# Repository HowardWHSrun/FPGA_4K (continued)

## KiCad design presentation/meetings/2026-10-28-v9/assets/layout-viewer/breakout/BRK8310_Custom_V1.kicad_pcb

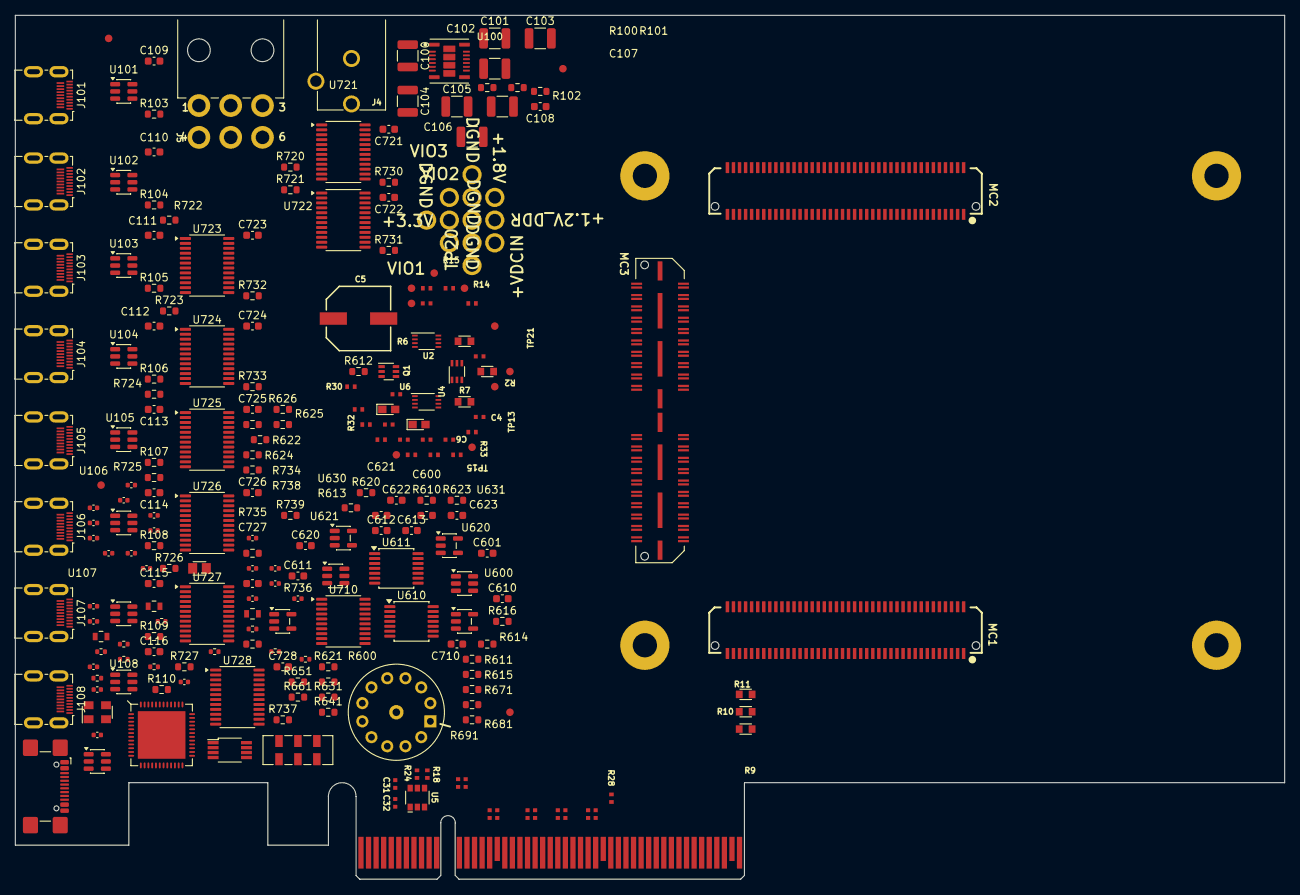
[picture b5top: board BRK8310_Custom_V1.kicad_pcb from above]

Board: 4 copper layers, 167.6 x 114.1 mm, 247 parts (0 on the bottom side), 224 nets, no tracks yet.

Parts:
C4: C0402C104K8PACTU; BRK8310_C4
C5: EEE-FK1E221P; BRK8310_C5
C6: TMK105BJ104KV-F; BRK8310_C6
C7: C0402C104K8PACTU; BRK8310_C7
C8: C0402C104K8PACTU; BRK8310_C8
C9: C0402C104K8PACTU; BRK8310_C9
C10: C0402C104K8PACTU; BRK8310_C10
C11: C0402C104K8PACTU; BRK8310_C11
C12: C0402C104K8PACTU; BRK8310_C12
C13: C0402C104K8PACTU; BRK8310_C13
C14: C0402C104K8PACTU; BRK8310_C14
C15: C0402C104K8PACTU; BRK8310_C15
C16: C0402C104K8PACTU; BRK8310_C16
C17: C0402C104K8PACTU; BRK8310_C17
C18: C0402C104K8PACTU; BRK8310_C18
C19: C0402C104K8PACTU; BRK8310_C19
C20: C0402C104K8PACTU; BRK8310_C20
C27: C0402C104K8PACTU; BRK8310_C27
C28: C0402C104K8PACTU; BRK8310_C28
C31: C0402C104K8PACTU; BRK8310_C31
C32: C0402C104K8PACTU; BRK8310_C32
C100, C101, C102, C103: 10uF 50V X7R; C_1210_3225Metric
C104, C105, C106, C107: 47uF 16V X6S; C_1210_3225Metric
C108: 47pF C0G; C_0603_1608Metric
C109, C110, C111, C112, C113, C114, C115, C116: 0.1uF 16V; C_0603_1608Metric
C500: 4.7u; C500
C501: 100n; C501
C502: 100n; C502
C503: 18p; C503
C504: 18p; C504
C505: 100n; C505
C506: 10n; C506
C507: 4.7u; C507
C508: 100n; C508
C509: 100n; C509
C510: 100n; C510
C511: 100n; C511
C512: 4.7u; C512
C513: 4.7u; C513
C514: 100n; C514
C515: 4.7u; C515
C516: 100n; C516
C517: 100n; C517
C518: 100n; C518
C519: 10n; C519
C520: 2.2uF 10V X7R; C520
C521: 2.2uF 10V X7R; C521
C600, C601: 2.2uF / 10V; C_0603_1608Metric
C610, C611, C612, C613, C620, C621, C622, C623, C710, C721, C722, C723, C724, C725, C726, C727, C728: 100nF / 16V; C_0603_1608Metric
D1: +3.3VDD; BRK8310_D1
D2: +VDC; BRK8310_D2
D500: USBLC6-2SC6; D500
FB500: 600R; FB500
FB501: 600R; FB501
FB502: 600R; FB502
FB503: 220R @100MHz; FB503
FID1: FIDUCIAL; BRK8310_FID1
FID2: FIDUCIAL; BRK8310_FID2
FID3: FIDUCIAL; BRK8310_FID3
FID4: FIDUCIAL; BRK8310_FID4
J4: PJ-102AH; BRK8310_J4
J5: 0455580003; BRK8310_J5
J6: PCIe x8 Card-Edge Connector; BRK8310_J6
J101, J102, J103, J104, J105, J106, J107, J108: Molex 467651001; HDMI_Micro-D_Molex_46765-1xxx
J500: USB4110-GF-A; J500
MC1: BTE-040-01-F-D-A; BRK8310_MC1
MC2: BTE-040-01-F-D-A; BRK8310_MC2
MC3: QTH-040-01-F-D-DP-A; BRK8310_MC3
MH1: MTG; BRK8310_MH1
MH2: MTG; BRK8310_MH2
MH3: MTG; BRK8310_MH3
MH4: MTG; BRK8310_MH4
Q1: SI1922EDH-T1-GE3; BRK8310_Q1
R2: CRCW06030000Z0EA; BRK8310_R2
R3: CRCW0402549RFKED; BRK8310_R3
R4: CRCW04022K00FKED; BRK8310_R4
R6: CRCW06030000Z0EA; BRK8310_R6
R7: CRCW06030000Z0EA; BRK8310_R7
R9: CRCW06030000Z0EA; BRK8310_R9
R10: CRCW06030000Z0EA; BRK8310_R10
R11: CRCW06030000Z0EA; BRK8310_R11
R13: CRCW0402200KFKED; BRK8310_R13
R14: CRCW04024K75FKED; BRK8310_R14
R15: CRCW04024K75FKED; BRK8310_R15
R18: CRCW0402100KFKED; BRK8310_R18
R23: CRCW0402200KFKED; BRK8310_R23
R24: CRCW0402100KFKED; BRK8310_R24
R25: CRCW0402100KFKED; BRK8310_R25
R28: CRCW04020000Z0ED; BRK8310_R28
R30: CRCW04024K75FKED; BRK8310_R30
R31: CRCW04024K75FKED; BRK8310_R31
R32: CRCW0402100KFKED; BRK8310_R32
R33: CRCW0402100KFKED; BRK8310_R33
R100: 23.2k 1%; R_0603_1608Metric
R101: 10k 1%; R_0603_1608Metric
R102: 17.4k 1%; R_0603_1608Metric
R103, R104, R105, R106, R107, R108, R109, R110: 37.4k 1%; R_0603_1608Metric
R500: 5.1k 1%; R500
R501: 5.1k 1%; R501
R502: 100k; R502
R503: 100k; R503
R504: 2k; R504
R505: 10k; R505
R506: 10k; R506
R507: 12k 1%; R507
R508: 10k; R508
R509: 10k; R509
R600, R610, R611, R620, R621, R631, R641, R651, R661, R671, R681, R691, R720, R721, R722, R723, R724, R725, R726, R727: 10k / 1%; R_0603_1608Metric
R612: 1M / 1%; R_0603_1608Metric
R613, R623: 100k / 1%; R_0603_1608Metric
R614, R615, R616, R624, R625, R626: 33R / 1%; R_0603_1608Metric
R622: 68k / 1%; R_0603_1608Metric
R730, R731, R732, R733, R734, R735, R736, R737: 1k / 1%; R_0603_1608Metric
R738: 140k / 0.1%; R_0603_1608Metric
R739: 49.9k / 0.1%; R_0603_1608Metric
SW600: Grayhill56P30_1P12T_N; Grayhill_56P30_1P12T_N
SW700: JS202011JCQN; SW700
TP1: +VDCIN; BRK8310_TP1
TP2: +3.3V; BRK8310_TP2
TP3: +1.8V; BRK8310_TP3
TP4: +1.2V_DDR; BRK8310_TP4
TP5: DGND; BRK8310_TP5
TP6: DGND; BRK8310_TP6
TP7: DGND; BRK8310_TP7
TP8: DGND; BRK8310_TP8
TP9: SMDAT_VIO; BRK8310_TP9
TP10: SMDAT_PCIE; BRK8310_TP10
TP11: SMCLK_PCIE; BRK8310_TP11
TP12: SMCLK_VIO; BRK8310_TP12
TP13: PERST_VIO; BRK8310_TP13
TP14: PERST_PCIE; BRK8310_TP14
TP15: WAKE_VIO; BRK8310_TP15
TP16: WAKE_PCIE; BRK8310_TP16
TP17: VIO1; BRK8310_TP17
TP18: VIO2; BRK8310_TP18
TP19: VIO3; BRK8310_TP19
TP20: +12V_PCIE_C; BRK8310_TP20
TP21: FAULT; BRK8310_TP21
U2: PCA9306DCUR; BRK8310_U2
U4: SN74AXC1T45DCK; BRK8310_U4
U5: AP22653AW6-7; BRK8310_U5
U6: PCA9306DCUR; BRK8310_U6
U100: TPSM63606RDLR; TI_TPSM63606_RDL0020A_EVM
U101, U102, U103, U104, U105, U106, U107, U108: TPS2553DBVR; SOT-23-6
U501: FT232HQ; U501
U505: 93LC56B-E/MS; U505
U506: TLV75533PDBVR; U506
U600: TLV75518PDBVR; SOT-23-5
U610, U611: TXU0304PWR; TSSOP-14_4.4x5mm_P0.65mm
U620: TPS3808G18DBVR; SOT-23-6
U621: TPS3808G01DBVR; SOT-23-6
U630, U631: SN74LVC1G17DBVR; SOT-23-5
U710: SN74LVC540APWR; TSSOP-20_4.4x6.5mm_P0.65mm
U721, U722, U723, U724, U725, U726, U727, U728: TS3A27518EPWR; TSSOP-24_4.4x7.8mm_P0.65mm
Y500: 12MHz; Y500

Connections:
+1.2V_DDR: MC3.80, R2.2, TP4.1
+1.8V: C4.1, MC1.2, R612.1, TP3.1, U620.5
+3.3V: MC2.70, R3.2, R30.2, R31.2, TP2.1
+3.3VAUX_PCIE: C31.2, R13.2, R23.2, U5.6
+3.3VAUX_PCIE_C: C32.2, J6.B10, R18.2, U5.1
+3.3V_PCIE_C: C12.2, J6.A9, J6.A10, J6.B8, U4.6
+VDCIN: C5.1, C6.2, C100.1, C101.1, C102.1, C103.1, J4.1, J5.1, J5.2, J5.3, MC2.1, MC2.2, MC2.3, MC2.4, R4.2, TP1.1, U100.1, U100.14, U100.16
/B64_L17N: MC1.44, R11.2
/B64_L17P: MC1.42, R10.2
/B64_L20N: MC1.40, R9.2
/B67_T3U_N12: MC3.78, R7.2
/Frontend ports and power/FRONTEND_3V3: C104.1, C105.1, C106.1, C107.1, C108.2, C109.1, C110.1, C111.1, C112.1, C113.1, C114.1, C115.1, C116.1, R100.2, U100.5, U100.8, U100.9, U101.1, U101.3, U102.1, U102.3, U103.1, U103.3, U104.1, U104.3, U105.1, U105.3, U106.1, U106.3, U107.1, U107.3, U108.1, U108.3
/Frontend ports and power/P1_TCK: J101.17, R730.1, U721.11
/Frontend ports and power/P1_TDI: J101.15, U721.13
/Frontend ports and power/P1_TDO: J101.18, U721.17
/Frontend ports and power/P1_TMS: J101.2, U721.15
/Frontend ports and power/P1_VREF: J101.1, U721.18
/Frontend ports and power/P2_TCK: J102.17, R731.1, U722.11
/Frontend ports and power/P2_TDI: J102.15, U722.13
/Frontend ports and power/P2_TDO: J102.18, U722.17
/Frontend ports and power/P2_TMS: J102.2, U722.15
/Frontend ports and power/P2_VREF: J102.1, U722.18
/Frontend ports and power/P3_TCK: J103.17, R732.1, U723.11
/Frontend ports and power/P3_TDI: J103.15, U723.13
/Frontend ports and power/P3_TDO: J103.18, U723.17
/Frontend ports and power/P3_TMS: J103.2, U723.15
/Frontend ports and power/P3_VREF: J103.1, U723.18
/Frontend ports and power/P4_TCK: J104.17, R733.1, U724.11
/Frontend ports and power/P4_TDI: J104.15, U724.13
/Frontend ports and power/P4_TDO: J104.18, U724.17
/Frontend ports and power/P4_TMS: J104.2, U724.15
/Frontend ports and power/P4_VREF: J104.1, U724.18
/Frontend ports and power/P5_TCK: J105.17, R734.1, U725.11
/Frontend ports and power/P5_TDI: J105.15, U725.13
/Frontend ports and power/P5_TDO: J105.18, U725.17
/Frontend ports and power/P5_TMS: J105.2, U725.15
/Frontend ports and power/P5_VREF: J105.1, U725.18
/Frontend ports and power/P6_TCK: J106.17, R735.1, U726.11
/Frontend ports and power/P6_TDI: J106.15, U726.13
/Frontend ports and power/P6_TDO: J106.18, U726.17
/Frontend ports and power/P6_TMS: J106.2, U726.15
/Frontend ports and power/P6_VREF: J106.1, U726.18
/Frontend ports and power/P7_TCK: J107.17, R736.1, U727.11
/Frontend ports and power/P7_TDI: J107.15, U727.13
/Frontend ports and power/P7_TDO: J107.18, U727.17
/Frontend ports and power/P7_TMS: J107.2, U727.15
/Frontend ports and power/P7_VREF: J107.1, U727.18
/Frontend ports and power/P8_TCK: J108.17, R737.1, U728.11
/Frontend ports and power/P8_TDI: J108.15, U728.13
/Frontend ports and power/P8_TDO: J108.18, U728.17
/Frontend ports and power/P8_TMS: J108.2, U728.15
/Frontend ports and power/P8_VREF: J108.1, U728.18
/PCIE X4/+12V_PCIE_C: J6.A2, J6.A3, J6.B1, J6.B2, J6.B3, TP20.1
/PCIE X4/PCIE_PERST_B_3V3: J6.A11, TP14.1, U4.4
/PCIE X4/PCIE_PERST_VIO: C11.2, R2.1, U4.1
/PCIE X4/PCIE_PRSNT1_B: J6.A1, R28.2
/PCIE X4/PCIE_REFCLKN_C: C8.1, J6.A14
/PCIE X4/PCIE_REFCLKP_C: C7.1, J6.A13
/PCIE X4/PCIE_RX0N_C: C14.1, J6.A17
/PCIE X4/PCIE_RX0P_C: C13.1, J6.A16
/PCIE X4/PCIE_RX1N_C: C16.1, J6.A22
/PCIE X4/PCIE_RX1P_C: C15.1, J6.A21
/PCIE X4/PCIE_RX2N_C: C18.1, J6.A26
/PCIE X4/PCIE_RX2P_C: C17.1, J6.A25
/PCIE X4/PCIE_RX3N_C: C20.1, J6.A30
/PCIE X4/PCIE_RX3P_C: C19.1, J6.A29
/PCIE X4/PCIE_SMCLK_3V3: J6.B5, TP11.1, U2.5
/PCIE X4/PCIE_SMDAT_3V3: J6.B6, TP10.1, U2.6
/PCIE X4/PCIE_WAKE_B_3V3: J6.B11, TP16.1, U6.6
/PCIE X4/VIO_PG: Q1.3, R31.1, R32.2, U5.3
/PCIE_PERST_B_VIO: R7.1, TP13.1, U4.3
/PCIE_SMCLK_VIO: R11.1, R14.1, TP12.1, U2.4
/PCIE_SMDAT_VIO: R10.1, R15.1, TP9.1, U2.3
/PCIE_WAKE_B_VIO: R9.1, R25.1, TP15.1, U6.3
/USB JTAG and selection/FTDI3V3_PHY: C515.1, C516.1, FB501.2, U501.3
/USB JTAG and selection/FTDI3V3_PLL: C513.1, C514.1, FB500.2, U501.8
/USB JTAG and selection/FTDI5V_FILTERED: C500.1, C501.1, FB502.2, U501.40
/USB JTAG and selection/FTDI_EECLK: R503.2, U501.44, U505.2
/USB JTAG and selection/FTDI_EECS: R502.1, U501.45, U505.1
/USB JTAG and selection/FTDI_EEDATA: R504.1, U501.43, U505.3
/USB JTAG and selection/HS_SENSE_DIV: R738.2, R739.2, U621.5
/VREFP: MC2.79, R6.2
B64_L1N: J101.14, MC1.12
B64_L1P: J101.12, MC1.10
B64_L2N: J102.14, MC1.16
B64_L2P: J102.12, MC1.14
B64_L3N: J103.14, MC1.15
B64_L3P: J103.12, MC1.13
B64_L4N: J104.14, MC1.8
B64_L4P: J104.12, MC1.6
B64_L5N: J105.14, MC1.7
B64_L5P: J105.12, MC1.5
B64_L6N: J106.14, MC1.11
B64_L6P: J106.12, MC1.9
B64_L7N: J107.14, MC1.23
B64_L7P: J107.12, MC1.21
B64_L8N: J108.14, MC1.20
B64_L8P: J108.12, MC1.18
DGND: C4.2, C5.2, C6.1, C9.1, C10.1, C11.1, C12.1, C27.1, C28.1, C31.1, C32.1, C100.2, C101.2, C102.2, C103.2, C104.2, C105.2, C106.2, C107.2, C109.2, C110.2, C111.2, C112.2, C113.2, C114.2, C115.2, C116.2, C500.2, C501.2, C502.2, C503.2, C504.2, C505.2, C506.1, C507.2, C508.2, C509.2, C510.2, C511.2, C512.2, C513.2, C514.2, C515.2, C516.2, C517.1, C518.1, C519.2, C520.2, C521.2, C600.2, C601.2, C610.2, C611.2, C612.2, C613.2, C620.2, C621.2, C622.2, C623.2, C710.2, C721.2, C722.2, C723.2, C724.2, C725.2, C726.2, C727.2, C728.2, D1.1, D2.1, D500.2, FB503.1, J4.2, J5.4, J5.5, J5.6, J6.A4, J6.A12, J6.A15, J6.A18, J6.A20, J6.A23, J6.A24, J6.A27, J6.A28, J6.A31, J6.A34, J6.A37, J6.A38, J6.A41, J6.A42, J6.A45, J6.A46, J6.A49, J6.B4, J6.B7, J6.B13, J6.B16, J6.B18, J6.B21, J6.B22, J6.B25, J6.B26, J6.B29, J6.B32, J6.B35, J6.B36, J6.B39, J6.B40, J6.B43, J6.B44, J6.B47, J6.B49, J101.4, J101.7, J101.10, J101.13, J101.16, J102.4, J102.7, J102.10, J102.13, J102.16, J103.4, J103.7, J103.10, J103.13, J103.16, J104.4, J104.7, J104.10, J104.13, J104.16, J105.4, J105.7, J105.10, J105.13, J105.16, J106.4, J106.7, J106.10, J106.13, J106.16, J107.4, J107.7, J107.10, J107.13, J107.16, J108.4, J108.7, J108.10, J108.13, J108.16, J500.A1, J500.A12, J500.B1, J500.B12, MC1.3, MC1.29, MC1.30, MC1.59, MC1.60, MC1.77, MC1.78, MC2.5, MC2.6, MC2.7, MC2.8, MC2.33, MC2.34, MC2.67, MC2.68, MC2.73, MC3.0, Q1.1, Q1.4, R24.1, R32.1, R33.1, R101.2, R102.2, R103.2, R104.2, R105.2, R106.2, R107.2, R108.2, R109.2, R110.2, R500.1, R501.2, R502.2, R507.2, R600.2, R611.2, R612.2, R613.2, R621.1, R622.2, R623.2, R631.1, R641.1, R651.1, R661.1, R671.1, R681.1, R691.1, R730.2, R731.2, R732.2, R733.2, R734.2, R735.2, R736.2, R737.2, R739.1, SW700.3, TP5.1, TP6.1, TP7.1, TP8.1, U2.1, U4.2, U4.5, U5.2, U6.1, U100.6, U100.11, U100.17, U100.18, U100.19, U100.20, U101.2, U102.2, U103.2, U104.2, U105.2, U106.2, U107.2, U108.2, U501.4, U501.9, U501.10, U501.11, U501.22, U501.23, U501.35, U501.36, U501.41, U501.42, U501.47, U501.48, U501.PAD, U505.5, U506.2, U600.2, U610.7, U611.7, U620.2, U621.2, U630.3, U631.3, U710.1, U710.10, U710.19, U721.5, U722.5, U723.5, U724.5, U725.5, U726.5, U727.5, U728.5, Y500.2, Y500.4
FTDI3V3: C505.1, C507.1, C508.1, C509.1, C510.1, C511.1, C512.1, FB500.1, FB501.1, R503.1, R505.2, R506.1, R508.2, R509.2, U501.12, U501.24, U501.39, U501.46, U505.8
GNDADC: MC2.77, R6.1
HOST_TCK: U501.13, U610.2, U611.2
HOST_TDI: U501.14, U610.3, U611.3
HOST_TDO: R509.1, U501.15, U610.5, U611.5
HOST_TMS: U501.16, U610.4, U611.4
HS_MUX_DISABLE_1: R720.2, U710.18, U721.20
HS_MUX_DISABLE_2: R721.2, U710.17, U722.20
HS_MUX_DISABLE_3: R722.2, U710.16, U723.20
HS_MUX_DISABLE_4: R723.2, U710.15, U724.20
HS_MUX_DISABLE_5: R724.2, U710.14, U725.20
HS_MUX_DISABLE_6: R725.2, U710.13, U726.20
HS_MUX_DISABLE_7: R726.2, U710.12, U727.20
HS_MUX_DISABLE_8: R727.2, U710.11, U728.20
HS_TARGET_SENSE: R622.1, R738.1, U721.10, U722.10, U723.10, U724.10, U725.10, U726.10, U727.10, U728.10
HS_TCK_1V8: R624.2, U721.4, U722.4, U723.4, U724.4, U725.4, U726.4, U727.4, U728.4
HS_TDI_1V8: R625.2, U721.6, U722.6, U723.6, U724.6, U725.6, U726.6, U727.6, U728.6
HS_TDO_1V8: U611.10, U721.9, U722.9, U723.9, U724.9, U725.9, U726.9, U727.9, U728.9
HS_TMS_1V8: R626.2, U721.7, U722.7, U723.7, U724.7, U725.7, U726.7, U727.7, U728.7
HS_USB_OE: R623.1, U611.8, U631.4
JTAG_LOCAL_1V8: C601.1, C613.1, C623.1, U600.5, U610.14, U611.14
JTAG_LOGIC_3V3: C521.1, C600.1, C610.1, C611.1, C612.1, C620.1, C621.1, C622.1, C710.1, C721.1, C722.1, C723.1, C724.1, C725.1, C726.1, C727.1, C728.1, R610.1, R620.1, R720.1, R721.1, R722.1, R723.1, R724.1, R725.1, R726.1, R727.1, SW700.1, U506.5, U600.1, U600.3, U610.1, U611.1, U620.6, U621.6, U630.5, U631.5, U710.20, U721.8, U721.14, U721.24, U722.8, U722.14, U722.24, U723.8, U723.14, U723.24, U724.8, U724.14, U724.24, U725.8, U725.14, U725.24, U726.8, U726.14, U726.24, U727.8, U727.14, U727.24, U728.8, U728.14, U728.24
JTAG_TCK: MC2.76, R614.2
JTAG_TDI: MC2.74, R615.2
JTAG_TDO: MC2.71, U610.10
JTAG_TMS: MC2.72, R616.2
MGT_REFCLK1N_225_C: C8.2, MC3.19
MGT_REFCLK1P_225_C: C7.2, MC3.17
MGT_RXN0_225: J6.B28, MC3.23
MGT_RXN1_225: J6.B24, MC3.27
MGT_RXN2_225: J6.B20, MC3.31
MGT_RXN3_225: J6.B15, MC3.35
MGT_RXP0_225: J6.B27, MC3.21
MGT_RXP1_225: J6.B23, MC3.25
MGT_RXP2_225: J6.B19, MC3.29
MGT_RXP3_225: J6.B14, MC3.33
MGT_TXN0_225: C20.2, MC3.24
MGT_TXN1_225: C18.2, MC3.28
MGT_TXN2_225: C16.2, MC3.32
MGT_TXN3_225: C14.2, MC3.36
MGT_TXP0_225: C19.2, MC3.22
MGT_TXP1_225: C17.2, MC3.26
MGT_TXP2_225: C15.2, MC3.30
MGT_TXP3_225: C13.2, MC3.34
unnamed: C502.1, FB503.2, J500.M1, J500.M2, J500.M3, J500.M4
unnamed: D1.2, R3.1
unnamed: D2.2, R4.1
unnamed: J6.B31, R28.1
unnamed: J101.19, U101.6
unnamed: J102.19, U102.6
unnamed: J103.19, U103.6
unnamed: J104.19, U104.6
unnamed: J105.19, U105.6
unnamed: J106.19, U106.6
unnamed: J107.19, U107.6
unnamed: J108.19, U108.6
unnamed: J500.A5, R500.2
unnamed: J500.B5, R501.1
unnamed: Q1.5, Q1.6, R30.1
unnamed: R18.1, TP21.1, U5.4
unnamed: C10.2, R13.1, U2.7, U2.8
unnamed: R24.2, U5.5
unnamed: C28.2, R23.1, U6.7, U6.8
unnamed: U100.3, U100.4
unnamed: C108.1, R100.1, R101.1, U100.10
unnamed: R102.1, U100.12
unnamed: R103.1, U101.5
unnamed: R104.1, U102.5
unnamed: R105.1, U103.5
unnamed: R106.1, U104.5
unnamed: R107.1, U105.5
unnamed: R108.1, U106.5
unnamed: R109.1, U107.5
unnamed: R110.1, U108.5
unnamed: R508.1, U501.17
unnamed: C503.1, U501.1, Y500.1
unnamed: C504.1, U501.2, Y500.3
unnamed: R507.1, U501.5
unnamed: C518.2, U501.37
unnamed: C517.2, U501.38
unnamed: C519.1, R506.2, U501.34
unnamed: R504.2, R505.1, U505.4
unnamed: R614.1, U610.13
unnamed: R615.1, U610.12
unnamed: R616.1, U610.11
unnamed: R624.1, U611.13
unnamed: R625.1, U611.12
unnamed: R626.1, U611.11
unnamed: R610.2, U620.1, U630.2
unnamed: R620.2, U621.1, U631.2
P1_RXN: J101.5, MC3.3
P1_RXP: J101.3, MC3.1
P2_RXN: J102.5, MC3.7
P2_RXP: J102.3, MC3.5
P3_RXN: J103.5, MC3.11
P3_RXP: J103.3, MC3.9
P4_RXN: J104.5, MC3.15
P4_RXP: J104.3, MC3.13
P5_RXN: J105.5, MC3.43
P5_RXP: J105.3, MC3.41
P6_RXN: J106.5, MC3.47
P6_RXP: J106.3, MC3.45
P7_RXN: J107.5, MC3.51
P7_RXP: J107.3, MC3.49
P8_RXN: J108.5, MC3.55
P8_RXP: J108.3, MC3.53
SEL_0: R611.1, SW600.1, U620.3
SEL_1: R621.2, SW600.2, U710.2
SEL_2: R631.2, SW600.3, U710.3
SEL_3: R641.2, SW600.4, U710.4
SEL_4: R651.2, SW600.5, U710.5
SEL_5: R661.2, SW600.6, U710.6
SEL_6: R671.2, SW600.7, U710.7
SEL_7: R681.2, SW600.8, U710.8
SEL_8: R691.2, SW600.9, U710.9
USB5V: C506.2, C520.1, D500.5, FB502.1, J500.A4, J500.A9, J500.B4, J500.B9, U506.1, U506.3
USB_DM_CONN: D500.4, J500.A7, J500.B7
USB_DP_CONN: D500.6, J500.A6, J500.B6
USB_D_N: D500.3, U501.6
USB_D_P: D500.1, U501.7
USB_SELECT_ENABLE_3V3: R600.1, SW600.A, SW700.2, U621.3
VIO1: C9.2, C27.2, MC1.1, Q1.2, R14.2, R15.2, R25.2, R33.2, TP17.1, U2.2, U6.2
VIO2: MC1.80, TP18.1
VIO3: MC2.69, TP19.1
XEM_USB_OE: R613.1, U610.8, U630.4

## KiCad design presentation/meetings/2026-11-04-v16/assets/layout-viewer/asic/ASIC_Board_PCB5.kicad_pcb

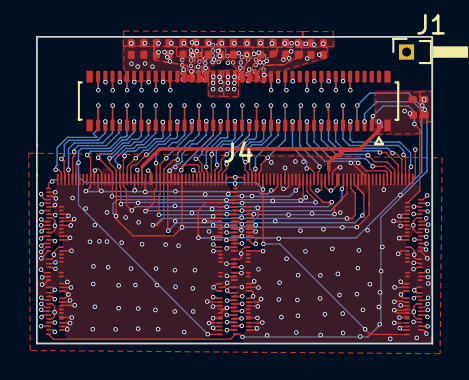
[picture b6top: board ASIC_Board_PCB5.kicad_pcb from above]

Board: 10 copper layers, 22.0 x 17.0 mm, 23 parts (1 on the bottom side), 72 nets.

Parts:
C1, C2, C4, C5, C6, C7, C14, C18, C19, C25, C26, C33, C34, C41, C42, C46, C48, C50: C_Small_US; C_0201_0603Metric
J1: Conn_01x01_Pin; PinHeader_1x01_P1.00mm_Horizontal
J3: Conn_02x40_Odd_Even; Hirose_DF40C-80DS-0.4V_2x40_P0.4mm
J4: Conn_02x40_Odd_Even; Hirose_DF40C-80DP-0.4V_2x40-1MP_P0.4mm
U01_BCD1, U01_BCD2: *; U01_BCD_OFF_CHIP

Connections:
/AC_IN: J3.69, J4.69, U01_BCD1.AC_IN, U01_BCD2.AC_IN
/AGND: C1.2, C2.2, C4.2, C5.2, C6.2, C18.2, C19.2, C25.2, C26.2, C33.2, C34.2, C41.2, C42.2, C46.2, C48.2, C50.2, J1.1 (Pin_1_1), J3.42, J3.44, J4.42, J4.44, U01_BCD1.AGND2, U01_BCD1.AGND_1, U01_BCD1.LAGND_1, U01_BCD1.LAGND_2, U01_BCD1.LAGND_3, U01_BCD1.LAGND_4, U01_BCD1.LAGND_5, U01_BCD1.LAGND_6, U01_BCD1.LAGND_7, U01_BCD1.LAGND_8, U01_BCD1.LAGND_9, U01_BCD1.LAGND_10, U01_BCD1.LAGND_11, U01_BCD1.LAGND_12, U01_BCD1.LAGND_13, U01_BCD1.LAGND_14, U01_BCD1.LAGND_15, U01_BCD1.LREF_GND1, U01_BCD1.LREF_GND2, U01_BCD1.LREF_GND3, U01_BCD1.LREF_GND4, U01_BCD1.RAGND_1, U01_BCD1.RAGND_2, U01_BCD1.RAGND_3, U01_BCD1.RAGND_4, U01_BCD1.RAGND_5, U01_BCD1.RAGND_6, U01_BCD1.RAGND_7, U01_BCD1.RAGND_8, U01_BCD1.RAGND_9, U01_BCD1.RAGND_10, U01_BCD1.RAGND_11, U01_BCD1.RAGND_12, U01_BCD1.RAGND_13, U01_BCD1.RAGND_14, U01_BCD1.RAGND_15, U01_BCD1.REF_1, U01_BCD1.REF_2, U01_BCD1.REF_3, U01_BCD1.REF_4, U01_BCD1.RREF_GND1, U01_BCD1.RREF_GND2, U01_BCD1.RREF_GND3, U01_BCD1.RREF_GND4, U01_BCD2.AGND2, U01_BCD2.AGND_1, U01_BCD2.LAGND_1, U01_BCD2.LAGND_2, U01_BCD2.LAGND_3, U01_BCD2.LAGND_4, U01_BCD2.LAGND_5, U01_BCD2.LAGND_6, U01_BCD2.LAGND_7, U01_BCD2.LAGND_8, U01_BCD2.LAGND_9, U01_BCD2.LAGND_10, U01_BCD2.LAGND_11, U01_BCD2.LAGND_12, U01_BCD2.LAGND_13, U01_BCD2.LAGND_14, U01_BCD2.LAGND_15, U01_BCD2.LREF_GND1, U01_BCD2.LREF_GND2, U01_BCD2.LREF_GND3, U01_BCD2.LREF_GND4, U01_BCD2.RAGND_1, U01_BCD2.RAGND_2, U01_BCD2.RAGND_3, U01_BCD2.RAGND_4, U01_BCD2.RAGND_5, U01_BCD2.RAGND_6, U01_BCD2.RAGND_7, U01_BCD2.RAGND_8, U01_BCD2.RAGND_9, U01_BCD2.RAGND_10, U01_BCD2.RAGND_11, U01_BCD2.RAGND_12, U01_BCD2.RAGND_13, U01_BCD2.RAGND_14, U01_BCD2.RAGND_15, U01_BCD2.REF_1, U01_BCD2.REF_2, U01_BCD2.REF_3, U01_BCD2.REF_4, U01_BCD2.RREF_GND1, U01_BCD2.RREF_GND2, U01_BCD2.RREF_GND3, U01_BCD2.RREF_GND4
/CHIP_RESET: J3.71, J4.71, U01_BCD1.RRST_DIGITAL, U01_BCD1.RST_DRIVER, U01_BCD2.RRST_DIGITAL, U01_BCD2.RST_DRIVER
/CLK32MHZ: J3.45, J4.45, U01_BCD1.CLK32MHZ
/CLK32MHZ(2): J3.19, J4.19, U01_BCD2.CLK32MHZ
/CLKH: J3.7, J4.7, U01_BCD1.CLKH, U01_BCD2.CLKH
/D<1>: J3.79, J4.79, U01_BCD1.DATAL<4>
/D<1>(2): J3.33, J4.33, U01_BCD2.DATAL<4>
/D<2>: J3.77, J4.77, U01_BCD1.DATAL<3>
/D<2>(2): J3.31, J4.31, U01_BCD2.DATAL<3>
/D<3>: J3.75, J4.75, U01_BCD1.DATAL<2>
/D<3>(2): J3.29, J4.29, U01_BCD2.DATAL<2>
/D<4>: J3.73, J4.73, U01_BCD1.DATAL<1>
/D<4>(2): J3.27, J4.27, U01_BCD2.DATAL<1>
/D<5>: J3.43, J4.43, U01_BCD1.DATAR<4>
/D<5>(2): J3.17, J4.17, U01_BCD2.DATAR<4>
/D<6>: J3.41, J4.41, U01_BCD1.DATAR<3>
/D<6>(2): J3.15, J4.15, U01_BCD2.DATAR<3>
/D<7>: J3.39, J4.39, U01_BCD1.DATAR<2>
/D<7>(2): J3.13, J4.13, U01_BCD2.DATAR<2>
/D<8>: J3.37, J4.37, U01_BCD1.DATAR<1>
/D<8>(2): J3.11, J4.11, U01_BCD2.DATAR<1>
/DGND: C7.2, C14.2, J3.46, J3.48, J4.46, J4.48, U01_BCD1.DGND1, U01_BCD1.DGND2, U01_BCD1.DGND3, U01_BCD1.DGND4, U01_BCD1.EN_LDO, U01_BCD1.LDGND_1, U01_BCD1.LDGND_2, U01_BCD1.LDGND_3, U01_BCD1.LDGND_4, U01_BCD1.LDGND_5, U01_BCD1.LDGND_6, U01_BCD1.LDGND_7, U01_BCD1.LDGND_8, U01_BCD1.LDGND_9, U01_BCD1.LDGND_10, U01_BCD1.LDGND_11, U01_BCD1.LDGND_12, U01_BCD1.LDGND_13, U01_BCD1.RDGND_1, U01_BCD1.RDGND_2, U01_BCD1.RDGND_3, U01_BCD1.RDGND_4, U01_BCD1.RDGND_5, U01_BCD1.RDGND_6, U01_BCD1.RDGND_7, U01_BCD1.RDGND_8, U01_BCD1.RDGND_9, U01_BCD1.RDGND_10, U01_BCD1.RDGND_11, U01_BCD1.RDGND_12, U01_BCD1.RDGND_13, U01_BCD2.DGND1, U01_BCD2.DGND2, U01_BCD2.DGND3, U01_BCD2.DGND4, U01_BCD2.EN_LDO, U01_BCD2.LDGND_1, U01_BCD2.LDGND_2, U01_BCD2.LDGND_3, U01_BCD2.LDGND_4, U01_BCD2.LDGND_5, U01_BCD2.LDGND_6, U01_BCD2.LDGND_7, U01_BCD2.LDGND_8, U01_BCD2.LDGND_9, U01_BCD2.LDGND_10, U01_BCD2.LDGND_11, U01_BCD2.LDGND_12, U01_BCD2.LDGND_13, U01_BCD2.RDGND_1, U01_BCD2.RDGND_2, U01_BCD2.RDGND_3, U01_BCD2.RDGND_4, U01_BCD2.RDGND_5, U01_BCD2.RDGND_6, U01_BCD2.RDGND_7, U01_BCD2.RDGND_8, U01_BCD2.RDGND_9, U01_BCD2.RDGND_10, U01_BCD2.RDGND_11, U01_BCD2.RDGND_12, U01_BCD2.RDGND_13
/DISC_OUT: J3.5, J4.5, U01_BCD1.DISC_OUT
/DISC_OUT(2): J3.3, J4.3, U01_BCD2.DISC_OUT
/DVDD: C7.1, C14.1, J3.34, J4.34, U01_BCD1.CGEN_RST, U01_BCD1.LDVDD_B1, U01_BCD1.LDVDD_B2, U01_BCD1.LDVDD_B3, U01_BCD1.LDVDD_T1, U01_BCD1.LDVDD_T2, U01_BCD1.LDVDD_T3, U01_BCD1.RDVDD_B1, U01_BCD1.RDVDD_B2, U01_BCD1.RDVDD_B3, U01_BCD1.RDVDD_T1, U01_BCD1.RDVDD_T2, U01_BCD1.RDVDD_T3, U01_BCD1.SPI_LDO_O, U01_BCD1.SPI_LDO_P, U01_BCD1.SPI_LDO_P1, U01_BCD1.SPI_LDO_P2, U01_BCD2.CGEN_RST, U01_BCD2.LDVDD_B1, U01_BCD2.LDVDD_B2, U01_BCD2.LDVDD_B3, U01_BCD2.LDVDD_T1, U01_BCD2.LDVDD_T2, U01_BCD2.LDVDD_T3, U01_BCD2.RDVDD_B1, U01_BCD2.RDVDD_B2, U01_BCD2.RDVDD_B3, U01_BCD2.RDVDD_T1, U01_BCD2.RDVDD_T2, U01_BCD2.RDVDD_T3, U01_BCD2.SPI_LDO_O, U01_BCD2.SPI_LDO_P, U01_BCD2.SPI_LDO_P1, U01_BCD2.SPI_LDO_P2
/FE_RESET: J3.65, J4.65, U01_BCD1.RST_FEL, U01_BCD1.RST_FER, U01_BCD2.RST_FEL, U01_BCD2.RST_FER
/IMP_TEST: J3.67, J4.67, U01_BCD1.IMP_TST, U01_BCD2.IMP_TST
/READ: J3.35, J4.35, U01_BCD1.READ
/READ(2): J3.9, J4.9, U01_BCD2.READ
/REF_VCM: C5.1, C46.1, J3.40, J4.40, U01_BCD1.LREF_VCM1, U01_BCD1.LREF_VCM2, U01_BCD1.LREF_VCM3, U01_BCD1.LREF_VCM4, U01_BCD1.RREF_VCM1, U01_BCD1.RREF_VCM2, U01_BCD1.RREF_VCM3, U01_BCD1.RREF_VCM4, U01_BCD1.VCM, U01_BCD2.LREF_VCM1, U01_BCD2.LREF_VCM2, U01_BCD2.LREF_VCM3, U01_BCD2.LREF_VCM4, U01_BCD2.RREF_VCM1, U01_BCD2.RREF_VCM2, U01_BCD2.RREF_VCM3, U01_BCD2.RREF_VCM4, U01_BCD2.VCM
/REF_VDD: C2.1, C33.1, J3.52, J4.52, U01_BCD1.LREF_VDD1, U01_BCD1.LREF_VDD2, U01_BCD1.LREF_VDD3, U01_BCD1.LREF_VDD4, U01_BCD1.RREF_VDD1, U01_BCD1.RREF_VDD2, U01_BCD1.RREF_VDD3, U01_BCD1.RREF_VDD4, U01_BCD2.LREF_VDD1, U01_BCD2.LREF_VDD2, U01_BCD2.LREF_VDD3, U01_BCD2.LREF_VDD4, U01_BCD2.RREF_VDD1, U01_BCD2.RREF_VDD2, U01_BCD2.RREF_VDD3, U01_BCD2.RREF_VDD4
/SPI_CLK: J3.63, J4.63, U01_BCD1.SPI_CLK, U01_BCD2.SPI_CLK
/SPI_DINL: J3.59, J4.59, U01_BCD1.SPI_DINL
/SPI_DINL(2): J3.25, J4.25, U01_BCD2.SPI_DINL
/SPI_DINR: J3.57, J4.57, U01_BCD1.SPI_DINR
/SPI_DINR(2): J3.23, J4.23, U01_BCD2.SPI_DINR
/SPI_LATCH: J3.61, J4.61, U01_BCD1.SPI_LATCH, U01_BCD2.SPI_LATCH
/STIM_CHB: J3.49, J4.49, U01_BCD1.FPGA_CHBL, U01_BCD1.FPGA_CHBR, U01_BCD2.FPGA_CHBL, U01_BCD2.FPGA_CHBR
/STIM_CLK: J3.53, J4.53, U01_BCD1.FPGA_CLK, U01_BCD2.FPGA_CLK
/STIM_EN: J3.51, J4.51, U01_BCD1.FPGA_EN, U01_BCD2.FPGA_EN
/STIM_START: J3.55, J4.55, U01_BCD1.FPGA_START, U01_BCD2.FPGA_START
/SYNC: J3.47, J4.47, U01_BCD1.SYNC
/SYNC(2): J3.21, J4.21, U01_BCD2.SYNC
/T_CLK32MHZ: J3.70, J4.70
/T_CLK32MHZ(2): J3.20, J4.20
/T_D<1>: J3.80, J4.80
/T_D<1>(2): J3.32, J4.32
/T_D<2>: J3.78, J4.78
/T_D<2>(2): J3.30, J4.30
/T_D<3>: J3.76, J4.76
/T_D<3>(2): J3.28, J4.28
/T_D<4>: J3.74, J4.74
/T_D<4>(2): J3.26, J4.26
/T_D<5>: J3.68, J4.68
/T_D<5>(2): J3.18, J4.18
/T_D<6>: J3.66, J4.66
/T_D<6>(2): J3.16, J4.16
/T_D<7>: J3.64, J4.64
/T_D<7>(2): J3.14, J4.14
/T_D<8>: J3.62, J4.62
/T_D<8>(2): J3.12, J4.12
/T_READ: J3.60, J4.60
/T_READ(2): J3.10, J4.10
/T_SYNC: J3.72, J4.72
/T_SYNC(2): J3.22, J4.22
/VDD10: C18.1, C19.1, J3.36, J4.36, U01_BCD1.P10_L, U01_BCD1.P10_R, U01_BCD2.P10_L, U01_BCD2.P10_R
/VDD_ADC: C1.1, C34.1, J3.56, J4.56, U01_BCD1.LVDD_ADC1, U01_BCD1.LVDD_ADC2, U01_BCD1.LVDD_ADC3, U01_BCD1.LVDD_ADC4, U01_BCD1.LVDD_ADC5, U01_BCD1.RVDD_ADC1, U01_BCD1.RVDD_ADC2, U01_BCD1.RVDD_ADC3, U01_BCD1.RVDD_ADC4, U01_BCD1.RVDD_ADC5, U01_BCD2.LVDD_ADC1, U01_BCD2.LVDD_ADC2, U01_BCD2.LVDD_ADC3, U01_BCD2.LVDD_ADC4, U01_BCD2.LVDD_ADC5, U01_BCD2.RVDD_ADC1, U01_BCD2.RVDD_ADC2, U01_BCD2.RVDD_ADC3, U01_BCD2.RVDD_ADC4, U01_BCD2.RVDD_ADC5
/VDD_CGEN: C6.1, C50.1, J3.1, J4.1, U01_BCD1.VDD_CGEN, U01_BCD2.VDD_CGEN
/VDD_DRIVER: C41.1, C42.1, J3.38, J4.38, U01_BCD1.LVDD_DRIVER1, U01_BCD1.LVDD_DRIVER2, U01_BCD1.LVDD_DRIVER3, U01_BCD1.LVDD_DRIVER4, U01_BCD1.LVDD_DRIVER5, U01_BCD1.RVDD_DRIVER1, U01_BCD1.RVDD_DRIVER2, U01_BCD1.RVDD_DRIVER3, U01_BCD1.RVDD_DRIVER4, U01_BCD1.RVDD_DRIVER5, U01_BCD2.LVDD_DRIVER1, U01_BCD2.LVDD_DRIVER2, U01_BCD2.LVDD_DRIVER3, U01_BCD2.LVDD_DRIVER4, U01_BCD2.LVDD_DRIVER5, U01_BCD2.RVDD_DRIVER1, U01_BCD2.RVDD_DRIVER2, U01_BCD2.RVDD_DRIVER3, U01_BCD2.RVDD_DRIVER4, U01_BCD2.RVDD_DRIVER5
/VDD_FE: C4.1, C48.1, J3.50, J4.50, U01_BCD1.LVDD_FE1, U01_BCD1.LVDD_FE2, U01_BCD1.LVDD_FE3, U01_BCD1.LVDD_FE4, U01_BCD1.RVDD_FE1, U01_BCD1.RVDD_FE2, U01_BCD1.RVDD_FE3, U01_BCD1.RVDD_FE4, U01_BCD2.LVDD_FE1, U01_BCD2.LVDD_FE2, U01_BCD2.LVDD_FE3, U01_BCD2.LVDD_FE4, U01_BCD2.RVDD_FE1, U01_BCD2.RVDD_FE2, U01_BCD2.RVDD_FE3, U01_BCD2.RVDD_FE4
/VSS10: C25.1, C26.1, J3.54, J4.54, U01_BCD1.M10_L, U01_BCD1.M10_R, U01_BCD2.M10_L, U01_BCD2.M10_R
